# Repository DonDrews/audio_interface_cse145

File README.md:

# USB Audio Interface

This repo contains firmware, schematics, and instructions for creating a functional audio interface usable cross-platform over USB. The current design supports one balanced XLR input with 80dB gain, and a 1/4 inch input with 40dB gain.

This design was created for the course CSE 145: Embedded Systems Design Project at UCSD in Spring 2022.

See [here](https://dondrews.github.io/posts/audio-interface/) for a writeup describing the final product.

## Electrical

Inside the [audio_interface](audio_interface) subfolder, there is a KiCAD project with both the schematic and layout for the custom PCB. For easier viewing, the [schematic](docs/audio_interface.pdf) and [layout](docs/audio_layout.pdf) are exported as pdfs as well. Note that many of the component choices were made due to the specific availability during the silicon shortage in Spring 2022. Other substitutes may be cheaper or easier to obtain in the future. To see the total list of necessary components, as well as what is currently in stock, check out the [Octopart BOM](https://octopart.com/bom-tool/Pp2dbWVm).

There is a [test log](https://docs.google.com/document/d/14NlvdZo9BEKJ16lZTaRw5GM3TA98BqlqD3HZuE-fhHs/edit?usp=sharing) which documents all the of the properties of the design, comparing the measured vs expected values. In addition, a listing at the bottom functions as a notebook to record which rework was performed on which day, and other observations.

## Audio Quality
There is a short recording demonstrating both inputs in the [docs](docs) directory. In addition, below is a frequency plot showing the results from recording a generated 1kHz sine wave on the instrument input. Currently the noise floor is low, but there is some distortion which can hopefully be resolved with further board modifications.

## Contributors

Many colleagues contributed to this project, and it could not have worked without their help with these sections:

- Ravi Johnson - electrical design reviews, assembly
- Devanshi Jain - electrical testing
- Seeraj Somla - systems engineering
- Nathan Hui, Christopher Crutchfield - advising

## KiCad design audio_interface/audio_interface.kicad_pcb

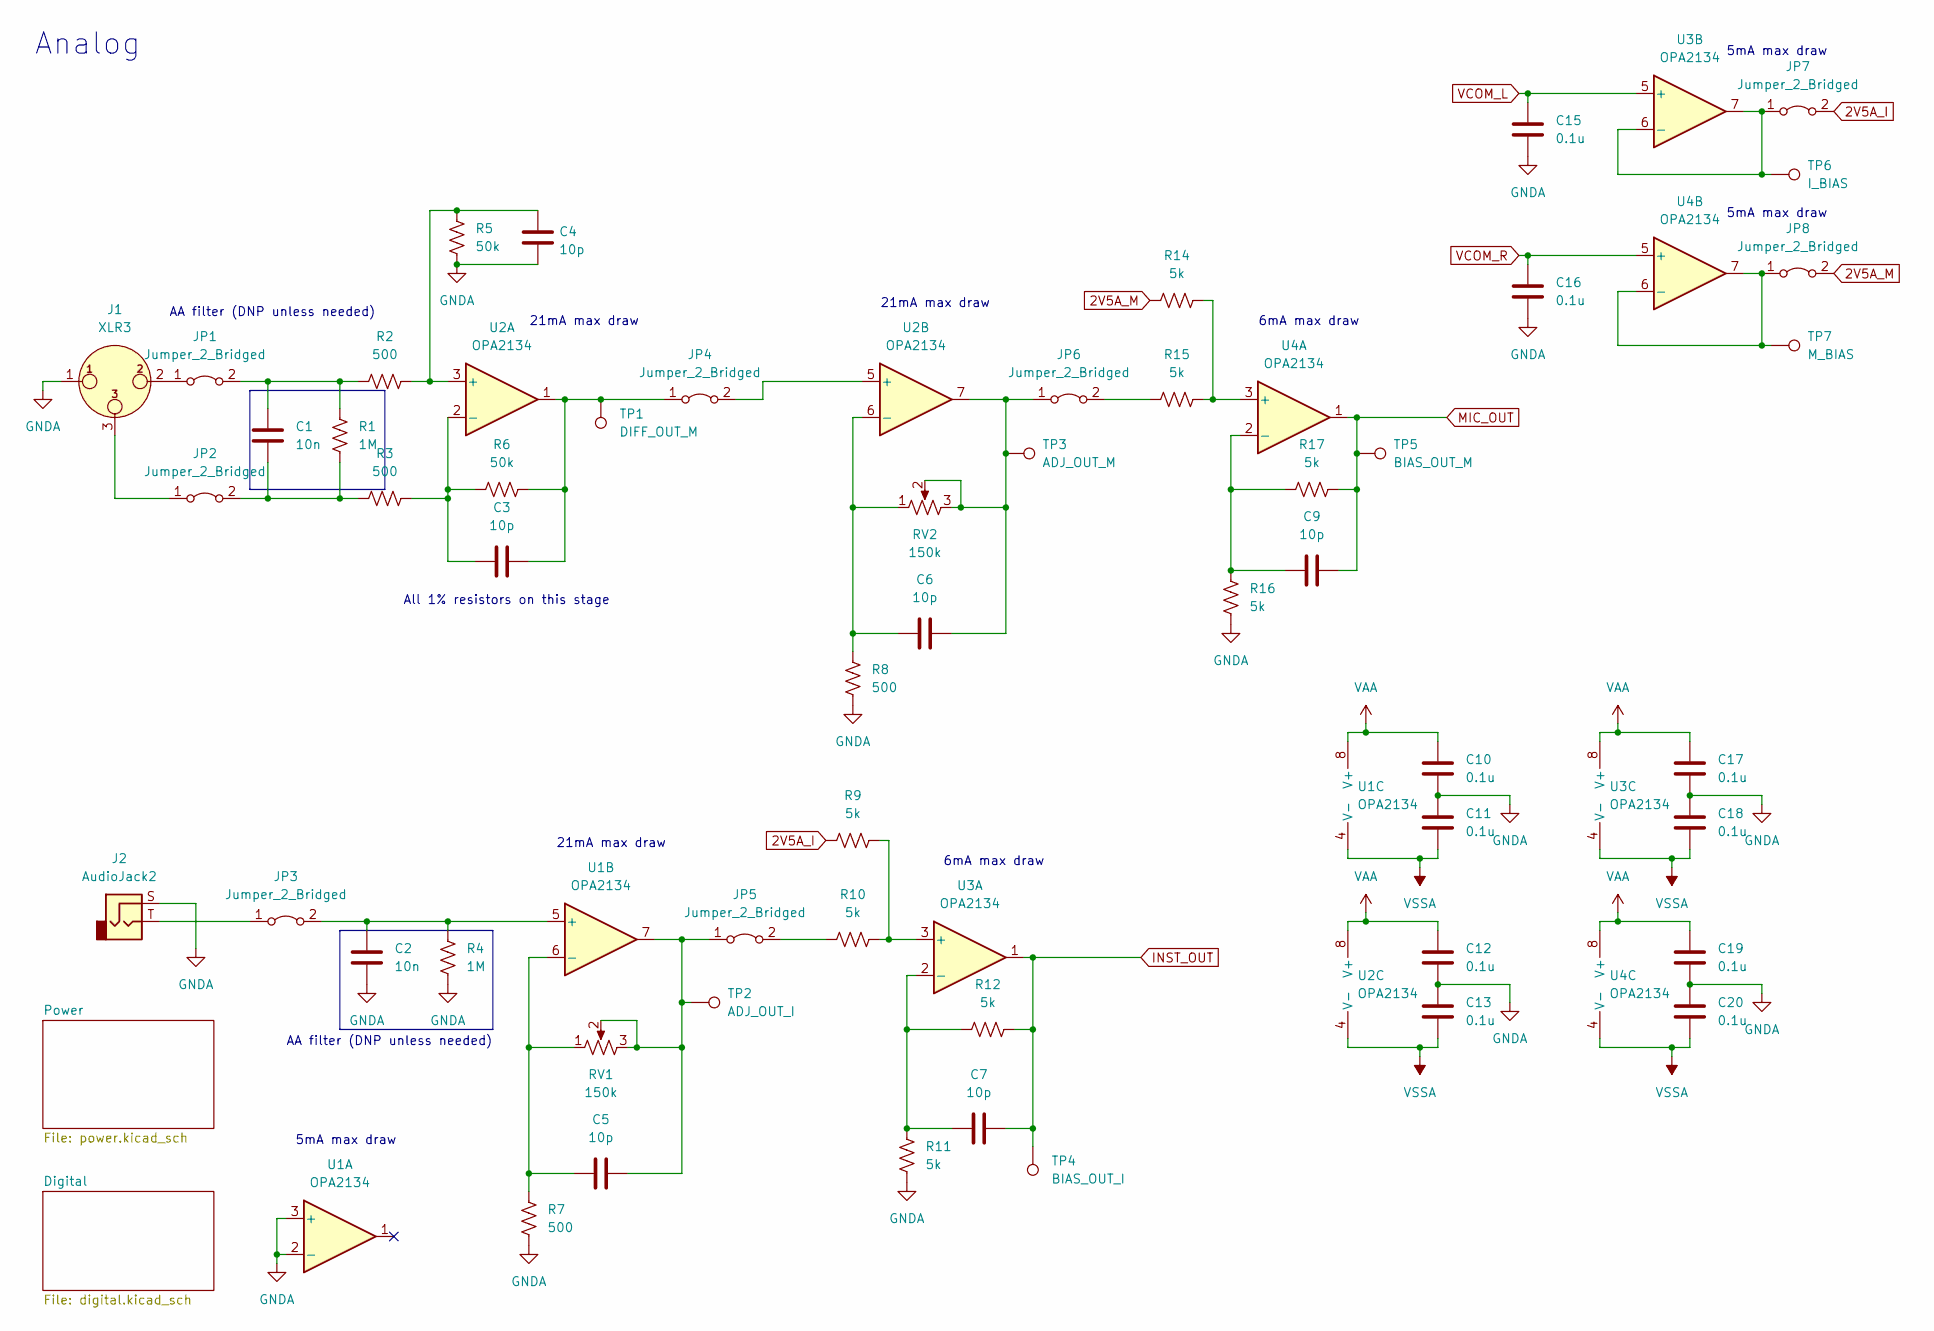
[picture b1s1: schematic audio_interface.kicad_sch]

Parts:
C1, C2: 10n; C_0805_2012Metric_Pad1.18x1.45mm_HandSolder
C3, C4, C5, C6, C7, C9: 10p; C_0805_2012Metric_Pad1.18x1.45mm_HandSolder
C10, C11, C12, C13, C15, C16, C17, C18, C19, C20: 0.1u; C_0805_2012Metric_Pad1.18x1.45mm_HandSolder
J1: XLR3; Jack_XLR_Neutrik_NC3FAAH-0_Horizontal
J2: AudioJack2; Jack_6.35mm_Neutrik_NMJ4HFD3_Horizontal
JP1, JP2, JP3, JP4, JP5, JP6, JP7, JP8: Jumper_2_Bridged; R_1206_3216Metric_Pad1.30x1.75mm_HandSolder
R1, R4: 1M; R_1206_3216Metric_Pad1.30x1.75mm_HandSolder
R2, R3, R7, R8: 500; R_1206_3216Metric_Pad1.30x1.75mm_HandSolder
R5, R6: 50k; R_1206_3216Metric_Pad1.30x1.75mm_HandSolder
R9, R10, R11, R12, R14, R15, R16, R17: 5k; R_1206_3216Metric_Pad1.30x1.75mm_HandSolder
RV1, RV2: 150k; PDB181-K420F-103A2
TP1: DIFF_OUT_M; TestPoint_Loop_D2.50mm_Drill1.0mm
TP2: ADJ_OUT_I; TestPoint_Loop_D2.50mm_Drill1.0mm
TP3: ADJ_OUT_M; TestPoint_Loop_D2.50mm_Drill1.0mm
TP4: BIAS_OUT_I; TestPoint_Loop_D2.50mm_Drill1.0mm
TP5: BIAS_OUT_M; TestPoint_Loop_D2.50mm_Drill1.0mm
TP6: I_BIAS; TestPoint_Loop_D2.50mm_Drill1.0mm
TP7: M_BIAS; TestPoint_Loop_D2.50mm_Drill1.0mm
U1, U2, U3, U4: OPA2134; DIP-8_W7.62mm_Socket

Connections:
2V5A_I: JP7.2 (B), R9.1; also elsewhere on the board
2V5A_M: JP8.2 (B), R14.1; also elsewhere on the board
GNDA: C2.2, C4.2, C10.2, C11.1, C12.2, C13.1, C15.2, C16.2, C17.2, C18.1, C19.2, C20.1, J1.1, J2.S, R4.2, R5.2, R7.2, R8.2, R11.2, R16.2, U1.2 (-), U1.3 (+); also elsewhere on the board
INST_OUT: C7.1, R12.2, TP4.1, U3.1; also elsewhere on the board
MIC_OUT: C9.2, R17.2, TP5.1, U4.1; also elsewhere on the board
unnamed: C1.1, JP1.2 (B), R1.1, R2.1
unnamed: C1.2, JP2.2 (B), R1.2, R3.1
unnamed: C2.1, JP3.2 (B), R4.1, U1.5 (+)
unnamed: C3.1, R3.2, R6.1, U2.2 (-)
unnamed: C3.2, JP4.1 (A), R6.2, TP1.1, U2.1
unnamed: C4.1, R2.2, R5.1, U2.3 (+)
unnamed: C5.1, JP5.1 (A), RV1.2, RV1.3, TP2.1, U1.7
unnamed: C5.2, R7.1, RV1.1, U1.6 (-)
unnamed: C6.1, JP6.1 (A), RV2.2, RV2.3, TP3.1, U2.7
unnamed: C6.2, R8.1, RV2.1, U2.6 (-)
unnamed: C7.2, R11.1, R12.1, U3.2 (-)
unnamed: C9.1, R16.1, R17.1, U4.2 (-)
unnamed: J1.2, JP1.1 (A)
unnamed: J1.3, JP2.1 (A)
unnamed: J2.T, JP3.1 (A)
unnamed: JP4.2 (B), U2.5 (+)
unnamed: JP5.2 (B), R10.1
unnamed: JP6.2 (B), R15.1
unnamed: JP7.1 (A), TP6.1, U3.6 (-), U3.7
unnamed: JP8.1 (A), TP7.1, U4.6 (-), U4.7
unnamed: R9.2, R10.2, U3.3 (+)
unnamed: R14.2, R15.2, U4.3 (+)
VAA: C10.1, C12.1, C17.1, C19.1, U1.8 (V+), U2.8 (V+), U3.8 (V+), U4.8 (V+); also elsewhere on the board
VCOM_L: C15.1, U3.5 (+); also elsewhere on the board
VCOM_R: C16.1, U4.5 (+); also elsewhere on the board
VSSA: C11.2, C13.2, C18.2, C20.2, U1.4 (V-), U2.4 (V-), U3.4 (V-), U4.4 (V-); also elsewhere on the board

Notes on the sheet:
21mA max draw
5mA max draw
6mA max draw
All 1% resistors on this stage
AA filter (DNP unless needed)
Analog

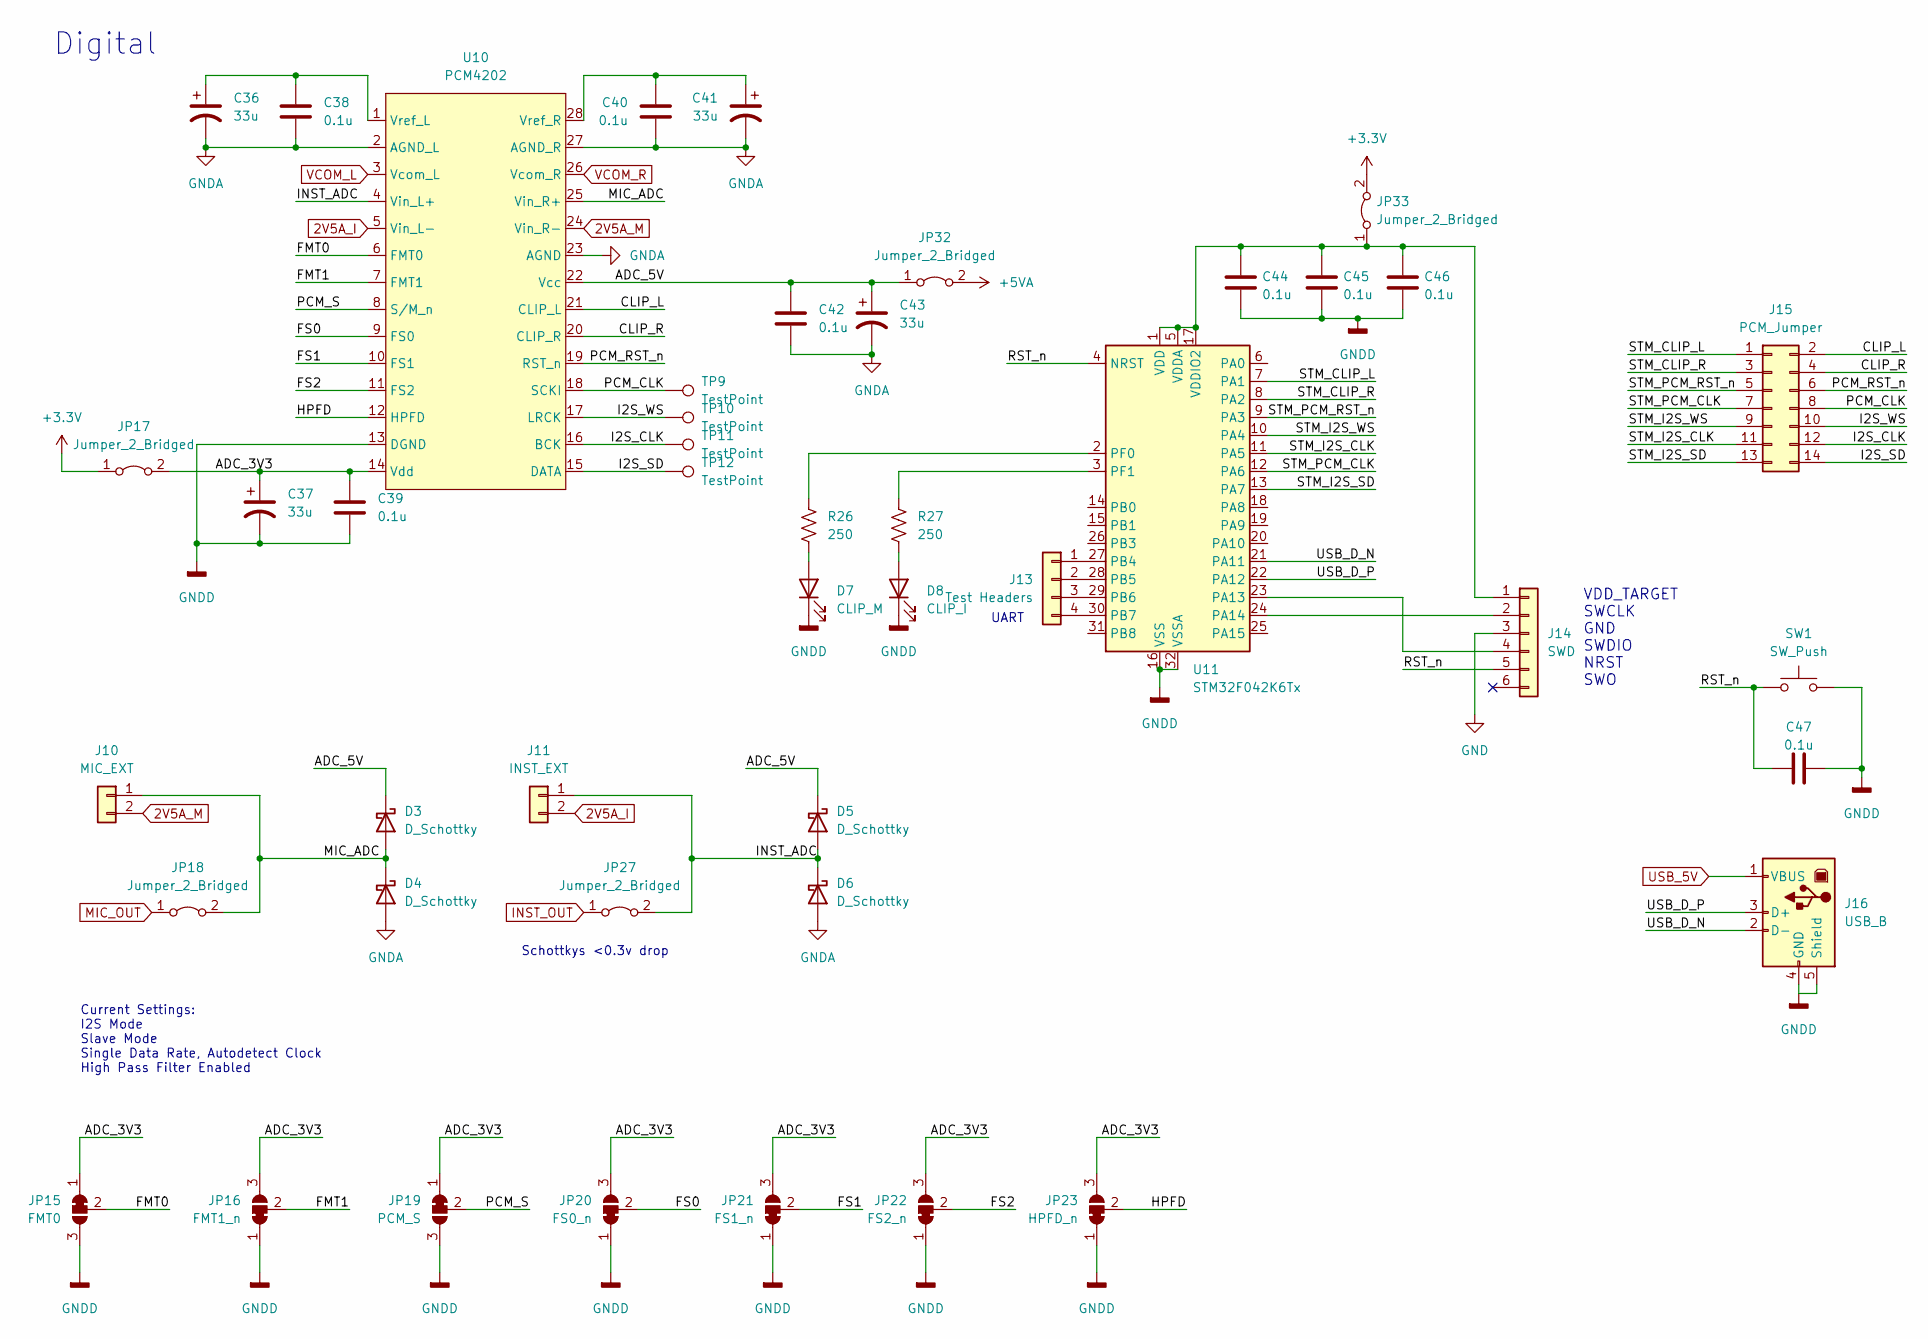
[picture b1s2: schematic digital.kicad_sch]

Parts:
C36, C37, C41, C43: 33u; CP_Elec_4x5.4
C38, C39, C40, C42, C44, C45, C46, C47: 0.1u; C_0805_2012Metric_Pad1.18x1.45mm_HandSolder
D3, D4, D5, D6: D_Schottky; D_1206_3216Metric_Pad1.42x1.75mm_HandSolder
D7: CLIP_M; LED_D3.0mm
D8: CLIP_I; LED_D3.0mm
J10: MIC_EXT; PinHeader_1x02_P2.54mm_Vertical
J11: INST_EXT; PinHeader_1x02_P2.54mm_Vertical
J13: Test Headers; PinHeader_1x04_P2.54mm_Vertical
J14: SWD; PinHeader_1x06_P2.54mm_Vertical
J15: PCM_Jumper; PinHeader_2x07_P2.54mm_Vertical
J16: USB_B; USB_B_Lumberg_2411_02_Horizontal
JP15: FMT0; SolderJumper-3_P1.3mm_Open_RoundedPad1.0x1.5mm_NumberLabels
JP16: FMT1_n; SolderJumper-3_P1.3mm_Open_RoundedPad1.0x1.5mm_NumberLabels
JP17, JP18, JP27, JP32, JP33: Jumper_2_Bridged; R_1206_3216Metric_Pad1.30x1.75mm_HandSolder
JP19: PCM_S; SolderJumper-3_P1.3mm_Open_RoundedPad1.0x1.5mm_NumberLabels
JP20: FS0_n; SolderJumper-3_P1.3mm_Open_RoundedPad1.0x1.5mm_NumberLabels
JP21: FS1_n; SolderJumper-3_P1.3mm_Open_RoundedPad1.0x1.5mm_NumberLabels
JP22: FS2_n; SolderJumper-3_P1.3mm_Open_RoundedPad1.0x1.5mm_NumberLabels
JP23: HPFD_n; SolderJumper-3_P1.3mm_Open_RoundedPad1.0x1.5mm_NumberLabels
R26, R27: 250; R_1206_3216Metric_Pad1.30x1.75mm_HandSolder
SW1: SW_Push; SW_PUSH_6mm
TP9, TP10, TP11, TP12: TestPoint; TestPoint_Pad_1.5x1.5mm
U10: PCM4202; SSOP-28_5.3x10.2mm_P0.65mm
U11: STM32F042K6Tx; LQFP-32_7x7mm_P0.8mm

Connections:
2V5A_I: J11.2, U10.5 (Vin_L-); also elsewhere on the board
2V5A_M: J10.2, U10.24 (Vin_R-); also elsewhere on the board
+3V3: JP17.1 (A), JP33.2 (B); also elsewhere on the board
+5VA: JP32.2 (B); also elsewhere on the board
/Digital/ADC_3V3: C37.1, C39.1, JP15.1 (A), JP16.3 (B), JP17.2 (B), JP19.1 (A), JP20.3 (B), JP21.3 (B), JP22.3 (B), JP23.3 (B), U10.14 (Vdd)
/Digital/ADC_5V: C42.1, C43.1, D3.1 (K), D5.1 (K), JP32.1 (A), U10.22 (Vcc)
/Digital/CLIP_L: J15.2, U10.21 (CLIP_L)
/Digital/CLIP_R: J15.4, U10.20 (CLIP_R)
/Digital/FMT0: JP15.2 (C), U10.6 (FMT0)
/Digital/FMT1: JP16.2 (C), U10.7 (FMT1)
/Digital/FS0: JP20.2 (C), U10.9 (FS0)
/Digital/FS1: JP21.2 (C), U10.10 (FS1)
/Digital/FS2: JP22.2 (C), U10.11 (FS2)
/Digital/HPFD: JP23.2 (C), U10.12 (HPFD)
/Digital/I2S_CLK: J15.12, TP11.1, U10.16 (BCK)
/Digital/I2S_SD: J15.14, TP12.1, U10.15 (DATA)
/Digital/I2S_WS: J15.10, TP10.1, U10.17 (LRCK)
/Digital/INST_ADC: D5.2 (A), D6.1 (K), J11.1, JP27.2 (B), U10.4 (Vin_L+)
/Digital/MIC_ADC: D3.2 (A), D4.1 (K), J10.1, JP18.2 (B), U10.25 (Vin_R+)
/Digital/PCM_CLK: J15.8, TP9.1, U10.18 (SCKI)
/Digital/PCM_RST_n: J15.6, U10.19 (RST_n)
/Digital/PCM_S: JP19.2 (C), U10.8 (S/M_n)
/Digital/RST_n: C47.1, J14.5, SW1.1, U11.4 (NRST)
/Digital/STM_CLIP_L: J15.1, U11.7 (PA1)
/Digital/STM_CLIP_R: J15.3, U11.8 (PA2)
/Digital/STM_I2S_CLK: J15.11, U11.11 (PA5)
/Digital/STM_I2S_SD: J15.13, U11.13 (PA7)
/Digital/STM_I2S_WS: J15.9, U11.10 (PA4)
/Digital/STM_PCM_CLK: J15.7, U11.12 (PA6)
/Digital/STM_PCM_RST_n: J15.5, U11.9 (PA3)
/Digital/USB_D_N: J16.2 (D-), U11.21 (PA11)
/Digital/USB_D_P: J16.3 (D+), U11.22 (PA12)
GND: J14.3
GNDA: C36.2, C37.2, C38.2, C39.2, C40.2, C41.2, C42.2, C43.2, C44.2, C45.2, C46.2, C47.2, D4.2 (A), D6.2 (A), D7.1 (K), D8.1 (K), J16.4 (GND), J16.5 (Shield), JP15.3 (B), JP16.1 (A), JP19.3 (B), JP20.1 (A), JP21.1 (A), JP22.1 (A), JP23.1 (A), SW1.2, U10.2 (AGND_L), U10.13 (DGND), U10.23 (AGND), U10.27 (AGND_R), U11.16 (VSS), U11.32 (VSSA); also elsewhere on the board
INST_OUT: JP27.1 (A); also elsewhere on the board
MIC_OUT: JP18.1 (A); also elsewhere on the board
unnamed: C36.1, C38.1, U10.1 (Vref_L)
unnamed: C40.1, C41.1, U10.28 (Vref_R)
unnamed: C44.1, C45.1, C46.1, J14.1, JP33.1 (A), U11.1 (VDD), U11.5 (VDDA), U11.17 (VDDIO2)
unnamed: D7.2 (A), R26.2
unnamed: D8.2 (A), R27.2
unnamed: J13.1, U11.27 (PB4)
unnamed: J13.2, U11.28 (PB5)
unnamed: J13.3, U11.29 (PB6)
unnamed: J13.4, U11.30 (PB7)
unnamed: J14.2, U11.24 (PA14)
unnamed: J14.4, U11.23 (PA13)
unnamed: R26.1, U11.2 (PF0)
unnamed: R27.1, U11.3 (PF1)
USB_5V: J16.1 (VBUS); also elsewhere on the board
VCOM_L: U10.3 (Vcom_L); also elsewhere on the board
VCOM_R: U10.26 (Vcom_R); also elsewhere on the board

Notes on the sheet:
Digital
Current Settings: I2S Mode Slave Mode Single Data Rate, Autodetect Clock High Pass Filter Enabled
Schottkys <0.3v drop
VDD_TARGET SWCLK GND SWDIO NRST SWO
UART

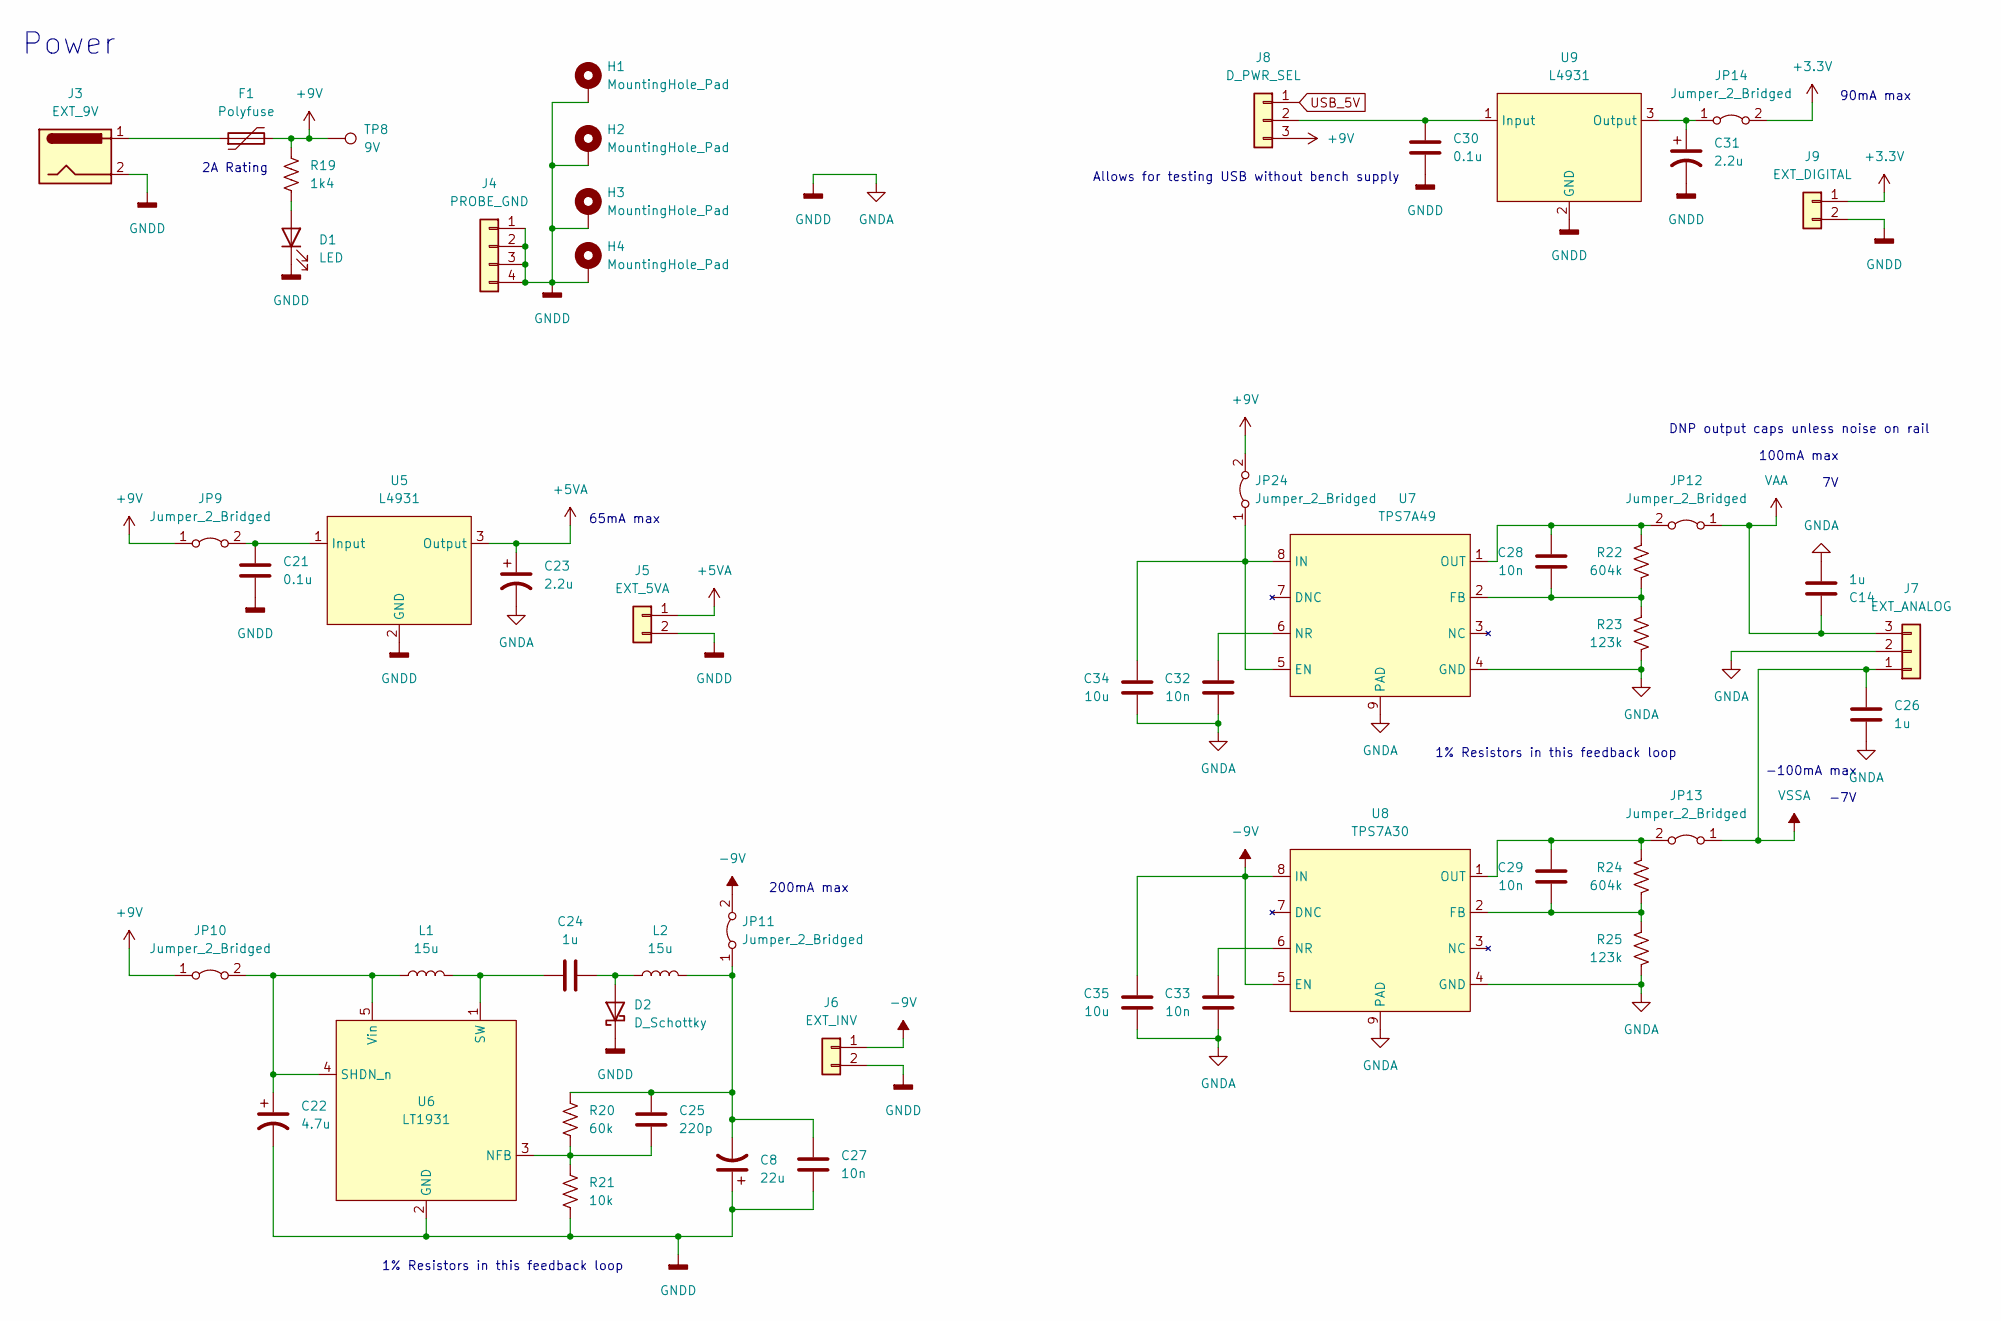
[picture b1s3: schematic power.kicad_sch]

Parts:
C8: 22u; CP_Elec_4x5.4
C14, C24, C26: 1u; C_1206_3216Metric_Pad1.33x1.80mm_HandSolder
C21, C30: 0.1u; C_0805_2012Metric_Pad1.18x1.45mm_HandSolder
C22: 4.7u; C_1206_3216Metric_Pad1.33x1.80mm_HandSolder
C23, C31: 2.2u; C_1206_3216Metric_Pad1.33x1.80mm_HandSolder
C25: 220p; C_0805_2012Metric_Pad1.18x1.45mm_HandSolder
C27, C28, C29, C32, C33: 10n; C_0805_2012Metric_Pad1.18x1.45mm_HandSolder
C34, C35: 10u; C_1206_3216Metric_Pad1.33x1.80mm_HandSolder
D1: LED; LED_1206_3216Metric_Pad1.42x1.75mm_HandSolder
D2: D_Schottky; D_1206_3216Metric_Pad1.42x1.75mm_HandSolder
F1: Polyfuse; Fuse_2920_7451Metric_Pad2.10x5.45mm_HandSolder
H1, H2, H3, H4: MountingHole_Pad; MountingHole_3.2mm_M3_Pad
J3: EXT_9V; BarrelJack_GCT_DCJ200-10-A_Horizontal
J4: PROBE_GND; PinHeader_1x04_P2.54mm_Vertical
J5: EXT_5VA; PinHeader_1x02_P2.54mm_Vertical
J6: EXT_INV; PinHeader_1x02_P2.54mm_Vertical
J7: EXT_ANALOG; PinHeader_1x03_P2.54mm_Vertical
J8: D_PWR_SEL; PinHeader_1x03_P2.54mm_Vertical
J9: EXT_DIGITAL; PinHeader_1x02_P2.54mm_Vertical
JP9, JP10, JP11, JP12, JP13, JP14, JP24: Jumper_2_Bridged; R_1206_3216Metric_Pad1.30x1.75mm_HandSolder
L1, L2: 15u; L_Taiyo-Yuden_NR-40xx_HandSoldering
R19: 1k4; R_1206_3216Metric_Pad1.30x1.75mm_HandSolder
R20: 60k; R_1206_3216Metric_Pad1.30x1.75mm_HandSolder
R21: 10k; R_1206_3216Metric_Pad1.30x1.75mm_HandSolder
R22, R24: 604k; R_1206_3216Metric_Pad1.30x1.75mm_HandSolder
R23, R25: 123k; R_1206_3216Metric_Pad1.30x1.75mm_HandSolder
TP8: 9V; TestPoint_Loop_D2.50mm_Drill1.0mm
U5, U9: L4931; TO-252-2
U6: LT1931; TSOT-23-5_HandSoldering
U7: TPS7A49; MSOP-8-1EP_3x3mm_P0.65mm_EP1.68x1.88mm_ThermalVias
U8: TPS7A30; MSOP-8-1EP_3x3mm_P0.65mm_EP1.68x1.88mm_ThermalVias

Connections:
+3V3: J9.1, JP14.2 (B); also elsewhere on the board
+5VA: C23.1, J5.1, U5.3 (Output); also elsewhere on the board
+9V: F1.2, J8.3, JP9.1 (A), JP10.1 (A), JP24.2 (B), R19.1, TP8.1
-9V: C35.1, J6.1, JP11.2 (B), U8.5 (EN), U8.8 (IN)
GNDA: C8.1, C14.2, C21.2, C22.2, C23.2, C26.2, C27.2, C30.2, C31.2, C32.2, C33.2, C34.2, C35.2, D1.1 (K), D2.1 (K), H1.1, H2.1, H3.1, H4.1, J3.2, J4.1, J4.2, J4.3, J4.4, J5.2, J6.2, J7.2, J9.2, R21.2, R23.2, R25.2, U5.2 (GND), U6.2 (GND), U7.4 (GND), U7.9 (PAD), U8.4 (GND), U8.9 (PAD), U9.2 (GND); also elsewhere on the board
unnamed: C21.1, JP9.2 (B), U5.1 (Input)
unnamed: C22.1, JP10.2 (B), L1.1, U6.4 (SHDN_n), U6.5 (Vin)
unnamed: C24.1, L1.2, U6.1 (SW)
unnamed: C24.2, D2.2 (A), L2.1
unnamed: C8.2, C25.1, C27.1, JP11.1 (A), L2.2, R20.1
unnamed: C25.2, R20.2, R21.1, U6.3 (NFB)
unnamed: C28.1, JP12.2 (B), R22.1, U7.1 (OUT)
unnamed: C28.2, R22.2, R23.1, U7.2 (FB)
unnamed: C29.1, JP13.2 (B), R24.1, U8.1 (OUT)
unnamed: C29.2, R24.2, R25.1, U8.2 (FB)
unnamed: C30.1, J8.2, U9.1 (Input)
unnamed: C31.1, JP14.1 (A), U9.3 (Output)
unnamed: C32.1, U7.6 (NR)
unnamed: C33.1, U8.6 (NR)
unnamed: C34.1, JP24.1 (A), U7.5 (EN), U7.8 (IN)
unnamed: D1.2 (A), R19.2
unnamed: F1.1, J3.1
USB_5V: J8.1; also elsewhere on the board
VAA: C14.1, J7.3, JP12.1 (A); also elsewhere on the board
VSSA: C26.1, J7.1, JP13.1 (A); also elsewhere on the board

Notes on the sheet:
100mA max
DNP output caps unless noise on rail
Allows for testing USB without bench supply
200mA max
65mA max
-7V
-100mA max
90mA max
Power
1% Resistors in this feedback loop
2A Rating

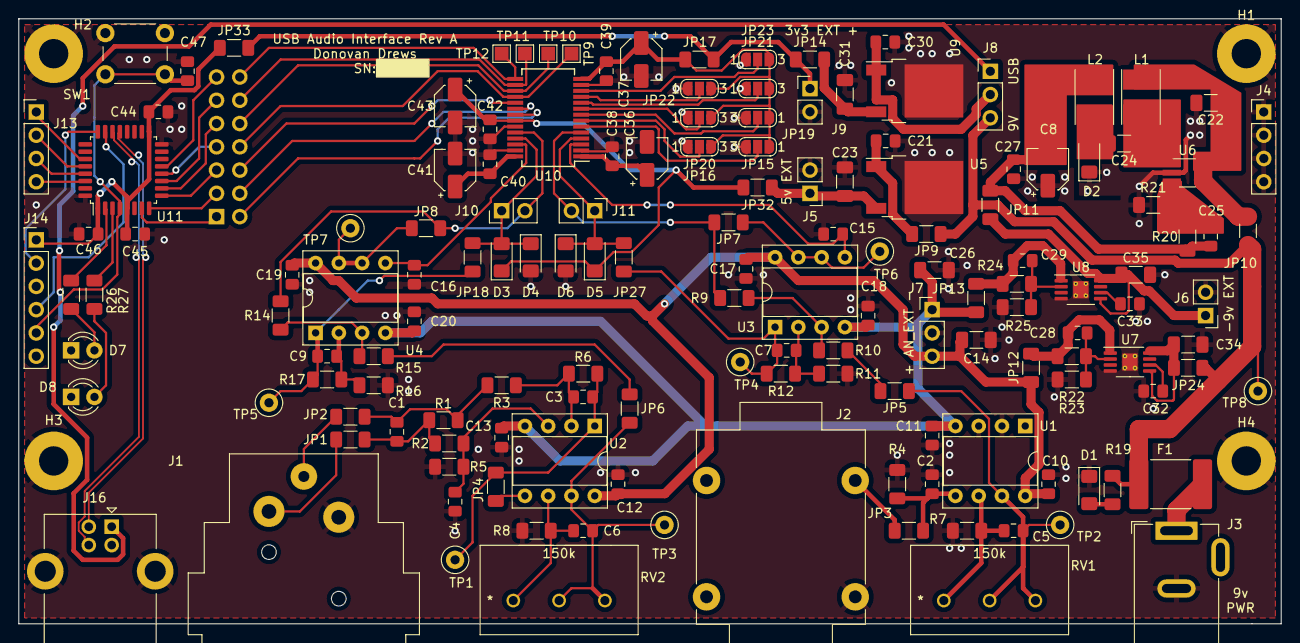
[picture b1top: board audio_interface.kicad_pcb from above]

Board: 2 copper layers, 137.8 x 66.0 mm, 155 parts (1 on the bottom side), 94 nets.

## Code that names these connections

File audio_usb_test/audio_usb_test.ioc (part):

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Mcu.Name=STM32F042K(4-6)Tx
Mcu.Package=LQFP32
Mcu.UserName=STM32F042K6Tx
PA1.Signal=GPIO_Input
PA11.Mode=Device
PA11.Signal=USB_DM
PA12.Mode=Device
PA12.Signal=USB_DP
PA13.Mode=Serial_Wire
PA13.Signal=SYS_SWDIO
PA14.Mode=Serial_Wire
PA14.Signal=SYS_SWCLK
PA2.Signal=GPIO_Input
PA3.Signal=GPIO_Output
PA4.Mode=Half_Duplex_Master
PA4.Signal=I2S1_WS
PA5.Mode=Half_Duplex_Master
PA5.Signal=I2S1_CK
PA7.Mode=Half_Duplex_Master
PA7.Signal=I2S1_SD
PB4.Signal=GPIO_Output
PB5.Signal=GPIO_Output
PB6.Signal=GPIO_Output
PB7.Signal=GPIO_Output
PF0-OSC_IN.Mode=HSE-External-Clock-Source
PF0-OSC_IN.Signal=RCC_OSC_IN
PF1-OSC_OUT.Signal=GPIO_Output
RCC.HSE_VALUE=12288000
RCC.SYSCLKFreq_VALUE=12288000
RCC.SYSCLKSource=RCC_SYSCLKSOURCE_HSE
board=custom

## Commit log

2022-04-11 Initial commit with parts selected, power setup.
2022-04-12 Further changes
2022-04-12 Added TP and fixed some capacitor values after SPICE sim.
2022-04-13 Added some footprints.
2022-04-13 Finished footprints.
2022-04-14 Orion's layout
2022-04-14 Fixed some layout issues. Flipped ADC.
2022-04-14 Fixed silkscreens
2022-04-14 Changed some footprints and grounding.
2022-04-14 Changed pin mappings for easier layout. Redid layout for better ground plane.
2022-04-15 Fixed some footprints, fixed silkscreen.
2022-04-15 Moved connectors to make flush with endplate. Ran DRC and fixed errors.
2022-04-15 Small grounding improvements
2022-04-15 Polygons for switching regulator. Silkscreen improvements,
2022-04-17 Added stm32 project.
2022-04-19 Working CDC example with stmf042 and tinyUSB.
2022-04-20 Added logging capabilities.
2022-04-20 Working audio 4 channel, but weird output.
2022-04-25 Fixed issue with 1 channel audio device. Recorded new log.
2022-05-01 Quick testing with HAL library. Edited tinyUSB to support isochronous. Still not working.
2022-05-02 Turned off serial output, which fixed an issue of event FIFO overflow due to CPU stalling.
2022-05-02 Added changes from tinyusb
2022-05-04 Added DMA for the I2S, and helper function to move into USB. Untested.
2022-05-08 Fixed 2 channel 24 bit descriptors.
2022-05-08 Fixed ordering of clock startup in order to make DMA work.
2022-05-09 Fixed issue with endianness and max packet size.
2022-05-10 Fixed bug with occasional errors. Caused by truncation in pma_alloc.
2022-05-10 Updated tinyusb commit.
2022-05-11 Fixed endianess issue. First fully working version.
2022-05-15 Removed debug insertions into audio stream. Added clipping LED code.
2022-05-15 Updated tinyusb
2022-05-19 Small README changes.
2022-05-20 Updated documentation.
2022-05-27 Changed to support external oscillator. Untested.
2022-06-01 Attempted external oscillator changes.
2023-12-14 Create LICENSE

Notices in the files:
parts and their libraries:
Copyright 2021 Accelerated Designs. All rights reserved.
